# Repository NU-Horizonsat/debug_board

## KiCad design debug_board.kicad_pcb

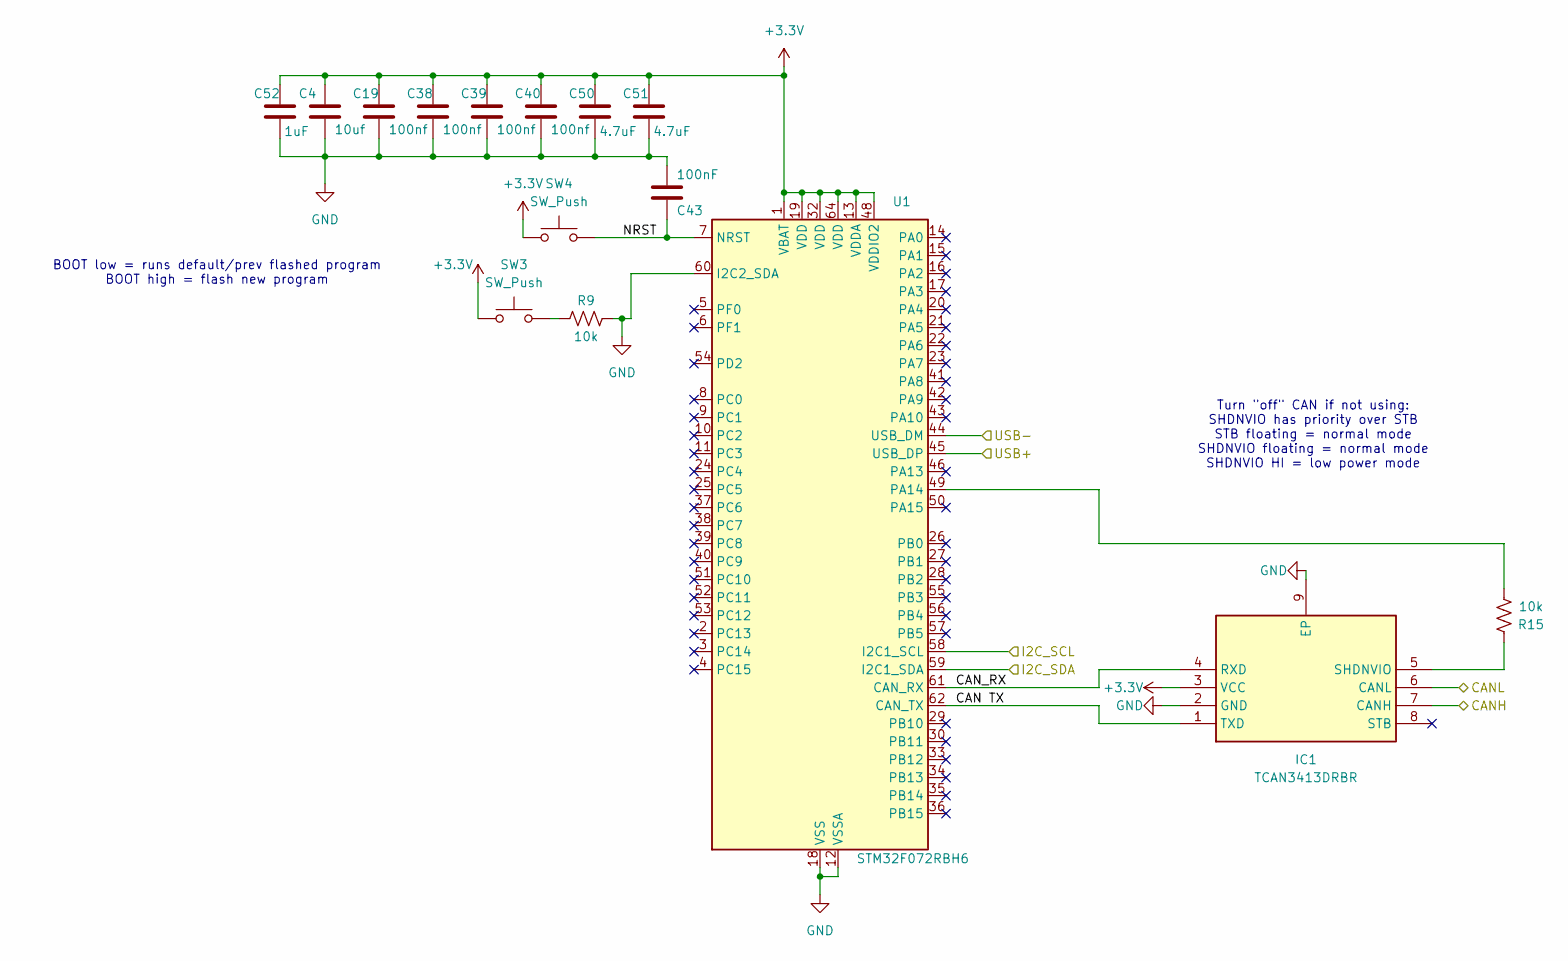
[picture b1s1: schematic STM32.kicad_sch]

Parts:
C4: 10uf; C_0603_1608Metric
C19, C38, C39, C40: 100nf; C_0603_1608Metric
C43: 100nF; C_0603_1608Metric
C50, C51: 4.7uF; C_0603_1608Metric
C52: 1uF; C_0603_1608Metric
IC1: TCAN3413DRBR; SON65P300X300X100-9N-D; Mouser Part Number 595-TCAN3413DRBR
R9, R15: 10k; R_0603_1608Metric
SW3, SW4: SW_Push; SW_Push_1P1T_XKB_TS-1187A
U1: STM32F072RBH6; LQFP-64_10x10mm_P0.5mm

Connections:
+3.3V: C4.1, C19.1, C38.1, C39.1, C40.1, C50.1, C51.1, C52.1, IC1.3 (VCC), SW3.1, SW4.1, U1.1 (VBAT), U1.13 (VDDA), U1.19 (VDD), U1.32 (VDD), U1.48 (VDDIO2), U1.64 (VDD); also elsewhere on the board
/Connector/CANH: IC1.7 (CANH); also elsewhere on the board
/Connector/CANL: IC1.6 (CANL); also elsewhere on the board
/Connector/I2C_SCL: U1.58 (I2C1_SCL); also elsewhere on the board
/Connector/I2C_SDA: U1.59 (I2C1_SDA); also elsewhere on the board
/STM32/CAN TX: IC1.1 (TXD), U1.62 (CAN_TX)
/STM32/CAN_RX: IC1.4 (RXD), U1.61 (CAN_RX)
/STM32/NRST: C43.2, SW4.2, U1.7 (NRST)
/STM32/USB+: U1.45 (USB_DP); also elsewhere on the board
/STM32/USB-: U1.44 (USB_DM); also elsewhere on the board
GND: C4.2, C19.2, C38.2, C39.2, C40.2, C43.1, C50.2, C51.2, C52.2, IC1.2 (GND), IC1.9 (EP), R9.2, U1.12 (VSSA), U1.18 (VSS), U1.31 (VSS), U1.47 (VSS), U1.60 (I2C2_SDA), U1.63 (VSS); also elsewhere on the board
unnamed: IC1.5 (SHDNVIO), R15.2
unnamed: R9.1, SW3.2
unnamed: R15.1, U1.49 (PA14)

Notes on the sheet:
BOOT low = runs default/prev flashed program BOOT high = flash new program
Turn "off" CAN if not using: SHDNVIO has priority over STB STB floating = normal mode SHDNVIO floating = normal mode SHDNVIO HI = low power mode

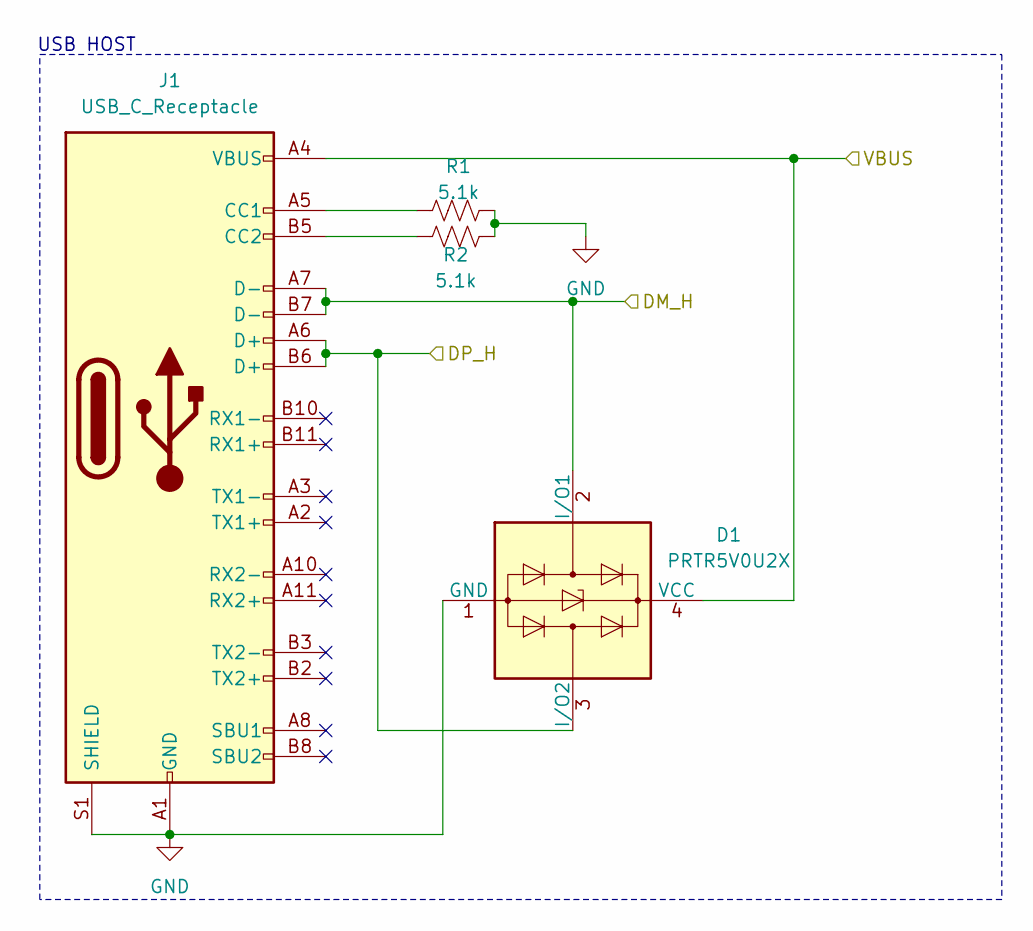
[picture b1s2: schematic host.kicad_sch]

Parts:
D1: PRTR5V0U2X; SOT-143
J1: USB_C_Receptacle; USB_C_Receptacle_HRO_TYPE-C-31-M-12
R1, R2: 5.1k; R_0603_1608Metric

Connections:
/USB Host/DM_H: D1.2 (I/O1), J1.A7 (D-), J1.B7 (D-); also elsewhere on the board
/USB Host/DP_H: D1.3 (I/O2), J1.A6 (D+), J1.B6 (D+); also elsewhere on the board
/USB Host/VBUS: D1.4 (VCC), J1.A4 (VBUS), J1.A9 (VBUS), J1.B4 (VBUS), J1.B9 (VBUS); also elsewhere on the board
GND: D1.1 (GND), J1.A1 (GND), J1.A12 (GND), J1.B1 (GND), J1.B12 (GND), J1.S1 (SHIELD), R1.2, R2.2; also elsewhere on the board
unnamed: J1.A5 (CC1), R1.1
unnamed: J1.B5 (CC2), R2.1

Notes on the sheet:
USB HOST

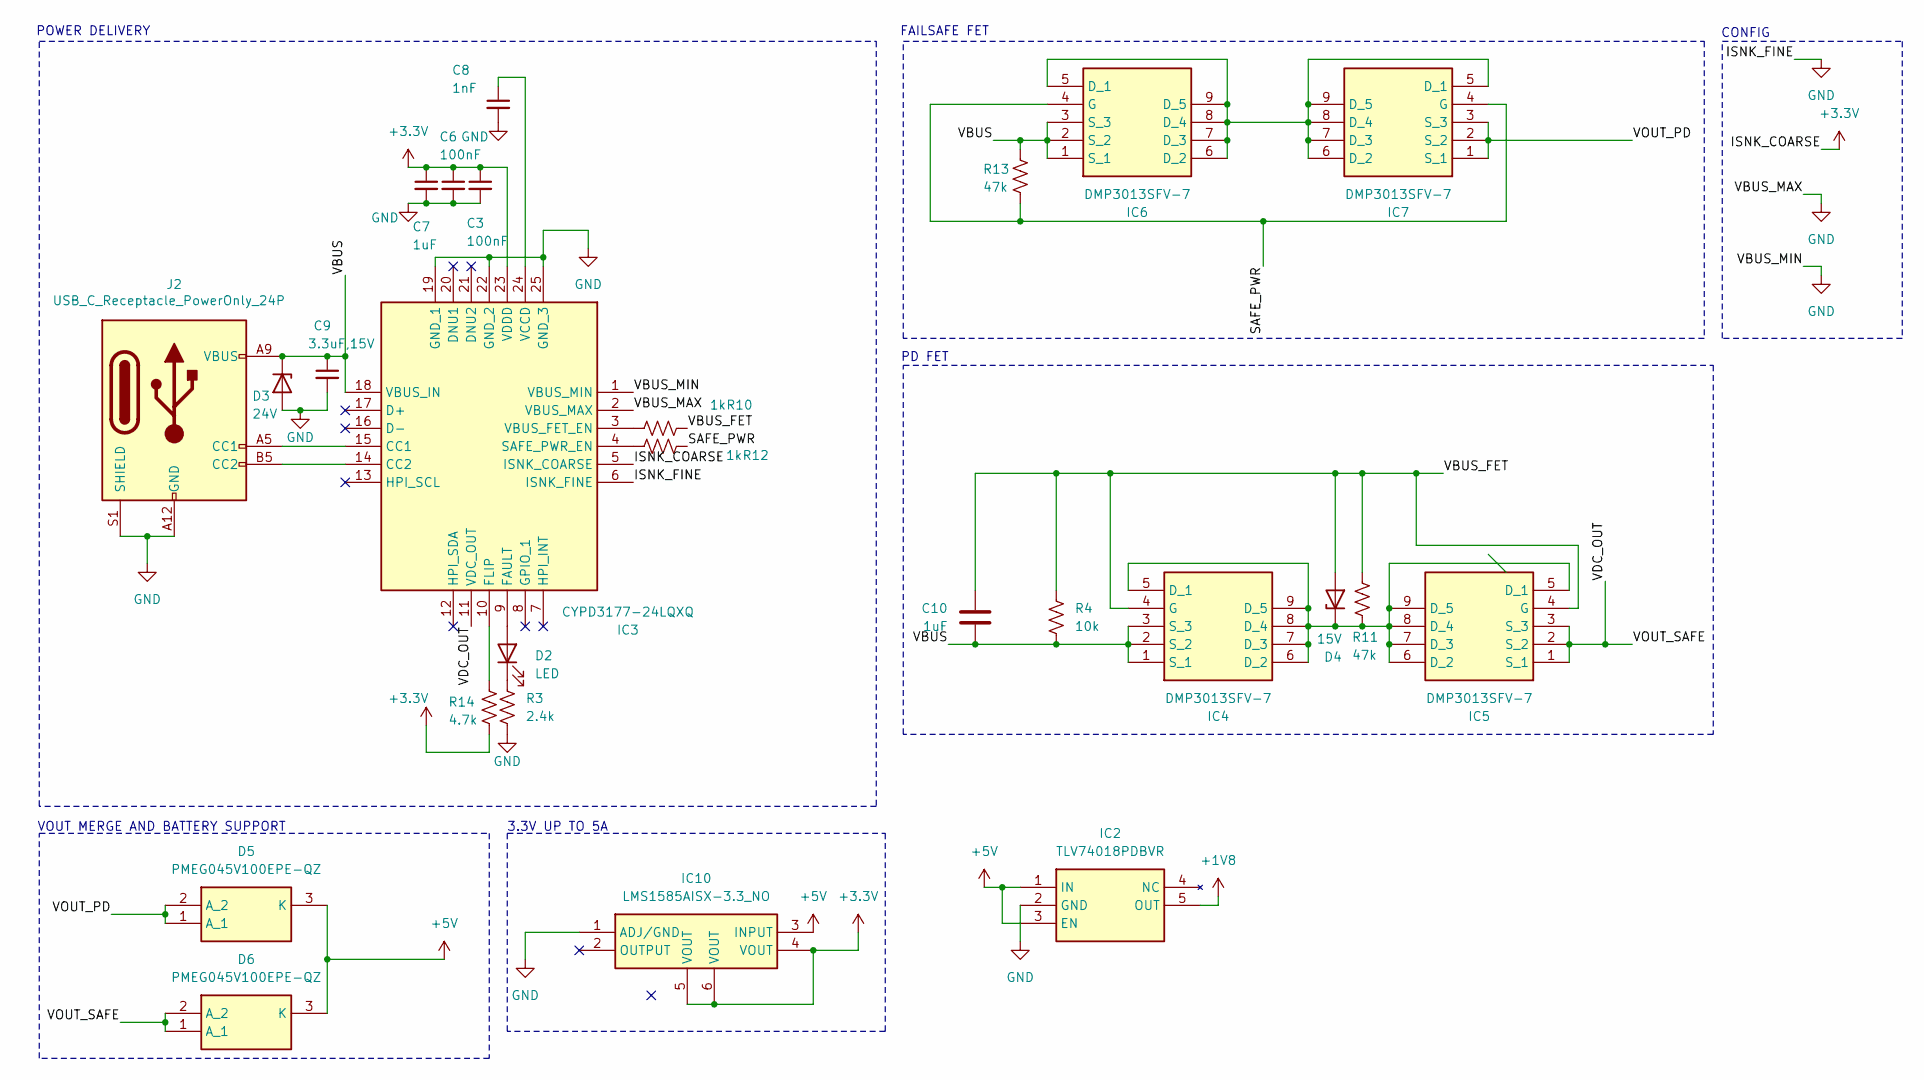
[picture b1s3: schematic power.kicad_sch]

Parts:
C3, C6: 100nF; C_0603_1608Metric
C7, C10: 1uF; C_0603_1608Metric
C8: 1nF; C_0603_1608Metric
C9: 3.3uF,15V; C_0603_1608Metric
D2: LED; LED_0603_1608Metric
D3: 24V; D_SOD-323_HandSoldering
D4: 15V; SODFL2513X100N
D5, D6: PMEG045V100EPE-QZ; PMEG045V100EPEQZ; Mouser Part Number 771-PMEG045V100EPEQZ
IC2: TLV74018PDBVR; SOT95P280X145-5N; Mouser Part Number 595-TLV74018PDBVR
IC3: CYPD3177-24LQXQ; QFN50P400X400X60-25N-D; Mouser Part Number 727-CYPD3177-24LQXQ
IC4, IC5, IC6, IC7: DMP3013SFV-7; DMP3036SFV7; Mouser Part Number 621-DMP3013SFV-7
IC10: LMS1585AISX-3.3_NO; KTT0003B; Mouser Part Number 595-LMS1585AISX33/NO
J2: USB_C_Receptacle_PowerOnly_24P; USB_C_Receptacle_GCT_USB4135-GF-A_6P_TopMnt_Horizontal
R3: 2.4k; R_0603_1608Metric
R4: 10k; R_0603_1608Metric
R10, R12: 1k; R_0603_1608Metric
R11, R13: 47k; R_0603_1608Metric
R14: 4.7k; R_0603_1608Metric

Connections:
+1V8: IC2.5 (OUT); also elsewhere on the board
+3.3V: C3.1, C6.1, C7.1, IC3.5 (ISNK_COARSE), IC3.23 (VDDD), IC10.4 (VOUT), IC10.5 (VOUT), IC10.6 (VOUT), R14.2; also elsewhere on the board
+5V: D5.3 (K), D6.3 (K), IC2.1 (IN), IC2.3 (EN), IC10.3 (INPUT); also elsewhere on the board
/Power/SAFE_PWR: IC6.4 (G), IC7.4 (G), R12.2, R13.2
/Power/VBUS: C9.1, C10.2, D3.1 (K), IC3.18 (VBUS_IN), IC4.1 (S_1), IC4.2 (S_2), IC4.3 (S_3), IC6.1 (S_1), IC6.2 (S_2), IC6.3 (S_3), J2.A4 (VBUS), J2.A9 (VBUS), J2.B4 (VBUS), J2.B9 (VBUS), R4.2, R13.1
/Power/VBUS_FET: C10.1, D4.2 (A), IC4.4 (G), IC5.4 (G), R4.1, R10.2, R11.1
/Power/VDC_OUT: D6.1 (A_1), D6.2 (A_2), IC3.11 (VDC_OUT), IC5.1 (S_1), IC5.2 (S_2), IC5.3 (S_3)
/Power/VOUT_PD: D5.1 (A_1), D5.2 (A_2), IC7.1 (S_1), IC7.2 (S_2), IC7.3 (S_3)
GND: C3.2, C6.2, C7.2, C8.2, C9.2, D3.2 (A), IC2.2 (GND), IC3.1 (VBUS_MIN), IC3.2 (VBUS_MAX), IC3.6 (ISNK_FINE), IC3.19 (GND_1), IC3.22 (GND_2), IC3.25 (GND_3), IC10.1 (ADJ/GND), J2.A1 (GND), J2.A12 (GND), J2.B1 (GND), J2.B12 (GND), J2.S1 (SHIELD), R3.2; also elsewhere on the board
unnamed: D2.2 (A), IC3.9 (FAULT)
unnamed: D2.1 (K), R3.1
unnamed: D4.1 (K), IC4.5 (D_1), IC4.6 (D_2), IC4.7 (D_3), IC4.8 (D_4), IC4.9 (D_5), IC5.5 (D_1), IC5.6 (D_2), IC5.7 (D_3), IC5.8 (D_4), IC5.9 (D_5), R11.2
unnamed: IC3.15 (CC1), J2.A5 (CC1)
unnamed: IC3.14 (CC2), J2.B5 (CC2)
unnamed: IC3.10 (FLIP), R14.1
unnamed: IC3.4 (SAFE_PWR_EN), R12.1
unnamed: IC3.3 (VBUS_FET_EN), R10.1
unnamed: C8.1, IC3.24 (VCCD)
unnamed: IC6.5 (D_1), IC6.6 (D_2), IC6.7 (D_3), IC6.8 (D_4), IC6.9 (D_5), IC7.5 (D_1), IC7.6 (D_2), IC7.7 (D_3), IC7.8 (D_4), IC7.9 (D_5)

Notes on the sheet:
PD FET
POWER DELIVERY
VOUT MERGE AND BATTERY SUPPORT
CONFIG
3.3V UP TO 5A
FAILSAFE FET

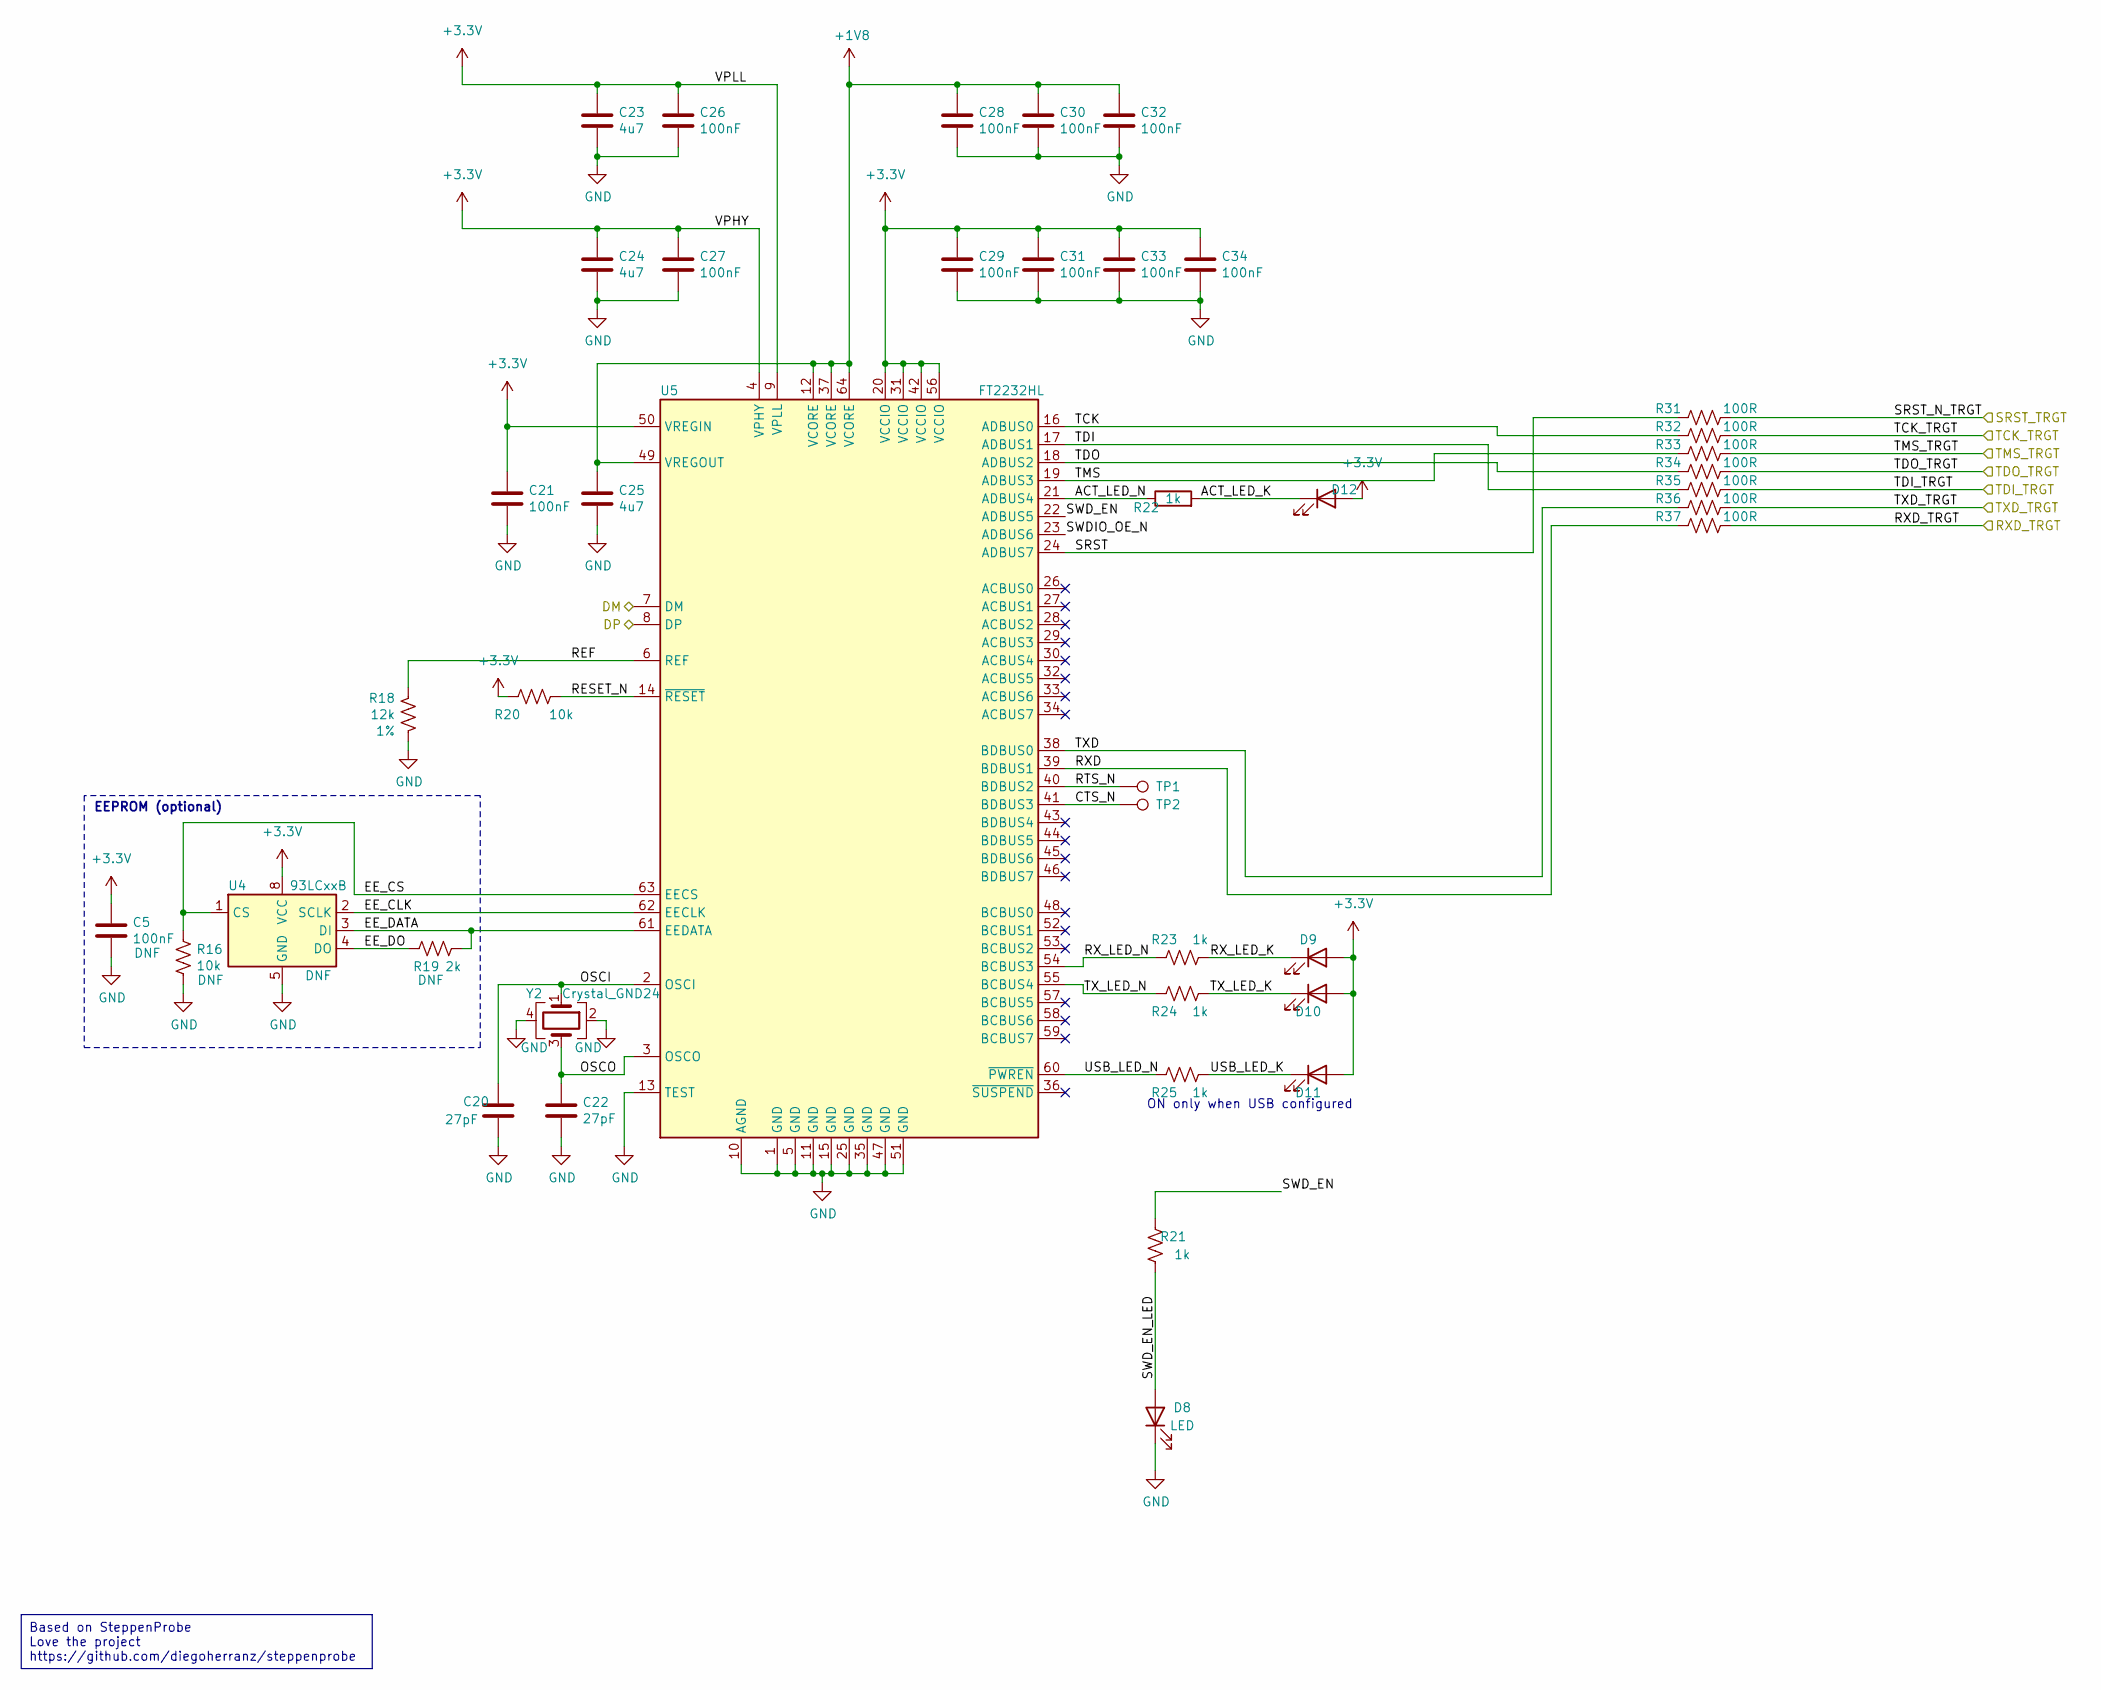
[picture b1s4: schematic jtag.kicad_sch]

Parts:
C5: 100nF; C_0603_1608Metric
C20, C22: 27pF; C_0603_1608Metric; Tolerance 5%; MPN C0603C270J5GAC; LCSC_PN C1656
C21, C26, C27, C28, C29, C30, C31, C32, C33, C34: 100nF; C_0603_1608Metric; Tolerance 10%; MPN CC0603KRX7R9BB104; LCSC_PN C14663
C23, C24, C25: 4u7; C_0603_1608Metric; Tolerance 10%; MPN CL10A475KO8NNNC; LCSC_PN C19666
D8, D9, D10, D11, D12: LED; LED_0603_1608Metric; MPN 19-217/GHC-YR1S2/3T; LCSC_PN C72043
R16: 10k; R_0603_1608Metric
R18: 12k; R_0603_1608Metric; Tolerance 1%; LCSC_PN C22790
R19: 2k; R_0603_1608Metric
R20: 10k; R_0603_1608Metric; Tolerance 5%; LCSC_PN C25804
R21, R22, R23, R24, R25: 1k; R_0603_1608Metric; Tolerance 5%; LCSC_PN C21190
R31, R32, R33, R34, R35, R36, R37: 100R; R_0603_1608Metric; Tolerance 5%; LCSC_PN C22775
TP1, TP2: TestPoint; TestPoint_Pad_D1.0mm
U4: 93LCxxB; SOIC-8_3.9x4.9mm_P1.27mm
U5: FT2232HL; LQFP-64_10x10mm_P0.5mm; MPN FT2232HL; LCSC_PN C27882
Y2: Crystal_GND24; Crystal_SMD_3225-4Pin_3.2x2.5mm; Tolerance 10PPM; MPN ABM8-12.000MHZ-20-B1U-T; LCSC_PN C9002

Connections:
+1V8: C25.1, C28.1, C30.1, C32.1, U5.12 (VCORE), U5.37 (VCORE), U5.49 (VREGOUT), U5.64 (VCORE); also elsewhere on the board
+3.3V: C5.1, C21.1, C23.1, C24.1, C26.1, C27.1, C29.1, C31.1, C33.1, C34.1, D9.2 (A), D10.2 (A), D11.2 (A), D12.2 (A), R20.2, U4.8 (VCC), U5.4 (VPHY), U5.9 (VPLL), U5.20 (VCCIO), U5.31 (VCCIO), U5.42 (VCCIO), U5.50 (VREGIN), U5.56 (VCCIO); also elsewhere on the board
/FTDI/ACT_LED_K: D12.1 (K), R22.2
/FTDI/ACT_LED_N: R22.1, U5.21 (ADBUS4)
/FTDI/CTS_N: TP2.1, U5.41 (BDBUS3)
/FTDI/DM: U5.7 (DM); also elsewhere on the board
/FTDI/DP: U5.8 (DP); also elsewhere on the board
/FTDI/EE_CLK: U4.2 (SCLK), U5.62 (EECLK)
/FTDI/EE_CS: R16.1, U4.1 (CS), U5.63 (EECS)
/FTDI/EE_DATA: R19.2, U4.3 (DI), U5.61 (EEDATA)
/FTDI/EE_DO: R19.1, U4.4 (DO)
/FTDI/OSCI: C20.1, U5.2 (OSCI), Y2.1
/FTDI/OSCO: C22.1, U5.3 (OSCO), Y2.3
/FTDI/REF: R18.1, U5.6 (REF)
/FTDI/RESET_N: R20.1, U5.14 (~RESET)
/FTDI/RTS_N: TP1.1, U5.40 (BDBUS2)
/FTDI/RXD: R37.1, U5.39 (BDBUS1)
/FTDI/RXD_TRGT: R37.2; also elsewhere on the board
/FTDI/RX_LED_K: D9.1 (K), R23.1
/FTDI/RX_LED_N: R23.2, U5.54 (BCBUS3)
/FTDI/SRST: R31.2, U5.24 (ADBUS7)
/FTDI/SRST_N_TRGT: R31.1; also elsewhere on the board
/FTDI/SWDIO_OE_N: U5.23 (ADBUS6)
/FTDI/SWD_EN: R21.2, U5.22 (ADBUS5)
/FTDI/SWD_EN_LED: D8.2 (A), R21.1
/FTDI/TCK: R32.2, U5.16 (ADBUS0)
/FTDI/TCK_TRGT: R32.1; also elsewhere on the board
/FTDI/TDI: R35.2, U5.17 (ADBUS1)
/FTDI/TDI_TRGT: R35.1; also elsewhere on the board
/FTDI/TDO: R34.2, U5.18 (ADBUS2)
/FTDI/TDO_TRGT: R34.1; also elsewhere on the board
/FTDI/TMS: R33.2, U5.19 (ADBUS3)
/FTDI/TMS_TRGT: R33.1; also elsewhere on the board
/FTDI/TXD: R36.2, U5.38 (BDBUS0)
/FTDI/TXD_TRGT: R36.1; also elsewhere on the board
/FTDI/TX_LED_K: D10.1 (K), R24.1
/FTDI/TX_LED_N: R24.2, U5.55 (BCBUS4)
/FTDI/USB_LED_K: D11.1 (K), R25.1
/FTDI/USB_LED_N: R25.2, U5.60 (~PWREN)
GND: C5.2, C20.2, C21.2, C22.2, C23.2, C24.2, C25.2, C26.2, C27.2, C28.2, C29.2, C30.2, C31.2, C32.2, C33.2, C34.2, D8.1 (K), R16.2, R18.2, U4.5 (GND), U5.1 (GND), U5.5 (GND), U5.10 (AGND), U5.11 (GND), U5.13 (TEST), U5.15 (GND), U5.25 (GND), U5.35 (GND), U5.47 (GND), U5.51 (GND), Y2.2, Y2.4; also elsewhere on the board

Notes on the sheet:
Based on SteppenProbe Love the project https://github.com/diegoherranz/steppenprobe
EEPROM (optional)
ON only when USB configured

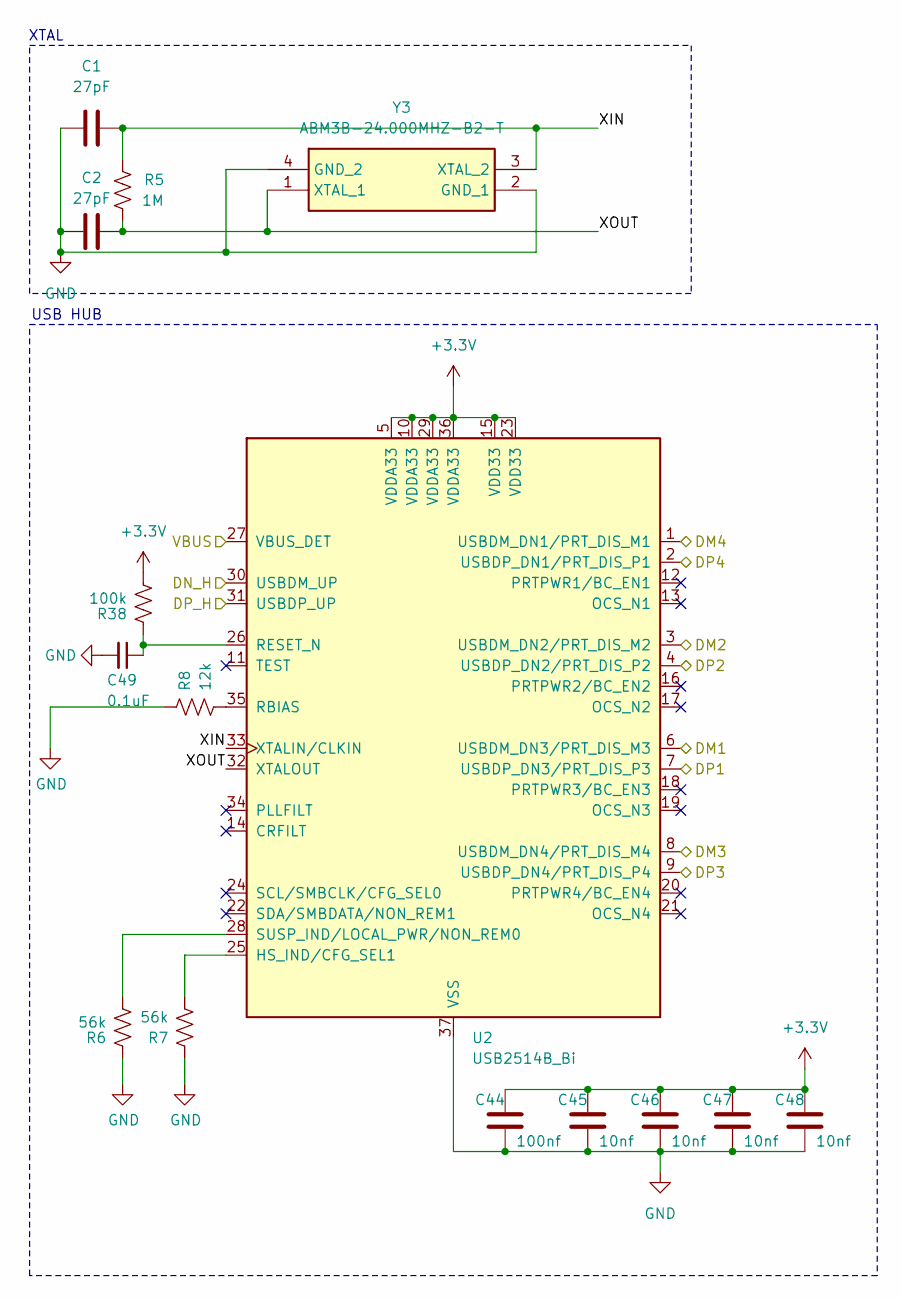
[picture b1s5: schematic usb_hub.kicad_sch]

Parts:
C1, C2: 27pF; C_0603_1608Metric
C44: 100nf; C_0603_1608Metric
C45, C46, C47, C48: 10nf; C_0603_1608Metric
C49: 0.1uF; C_0402_1005Metric
R5: 1M; R_0603_1608Metric
R6, R7: 56k; R_0603_1608Metric
R8: 12k; R_0603_1608Metric
R38: 100k; R_0603_1608Metric
U2: USB2514B_Bi; QFN-36-1EP_6x6mm_P0.5mm_EP3.7x3.7mm
Y3: ABM3B-24.000MHZ-B2-T; ABM3B; Mouser Part Number 815-ABM3B-24-B2

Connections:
+3.3V: C44.1, C45.1, C46.1, C47.1, C48.1, R38.2, U2.5 (VDDA33), U2.10 (VDDA33), U2.15 (VDD33), U2.23 (VDD33), U2.29 (VDDA33), U2.36 (VDDA33); also elsewhere on the board
/Connector/USB2+?: U2.9 (USBDP_DN4/PRT_DIS_P4); also elsewhere on the board
/Connector/USB2-?: U2.8 (USBDM_DN4/PRT_DIS_M4); also elsewhere on the board
/Connector/USB+: U2.4 (USBDP_DN2/PRT_DIS_P2); also elsewhere on the board
/Connector/USB-: U2.3 (USBDM_DN2/PRT_DIS_M2); also elsewhere on the board
/FTDI/DM: U2.6 (USBDM_DN3/PRT_DIS_M3); also elsewhere on the board
/FTDI/DP: U2.7 (USBDP_DN3/PRT_DIS_P3); also elsewhere on the board
/STM32/USB+: U2.2 (USBDP_DN1/PRT_DIS_P1); also elsewhere on the board
/STM32/USB-: U2.1 (USBDM_DN1/PRT_DIS_M1); also elsewhere on the board
/USB Host/DM_H: U2.30 (USBDM_UP); also elsewhere on the board
/USB Host/DP_H: U2.31 (USBDP_UP); also elsewhere on the board
/USB Host/VBUS: U2.27 (VBUS_DET); also elsewhere on the board
/USB Hub/XIN: C1.2, R5.1, U2.33 (XTALIN/CLKIN), Y3.3 (XTAL_2)
/USB Hub/XOUT: C2.2, R5.2, U2.32 (XTALOUT), Y3.1 (XTAL_1)
GND: C1.1, C2.1, C44.2, C45.2, C46.2, C47.2, C48.2, C49.2, R6.1, R7.1, R8.1, U2.37 (VSS), Y3.2 (GND_1), Y3.4 (GND_2); also elsewhere on the board
unnamed: R7.2, U2.25 (HS_IND/CFG_SEL1)
unnamed: R8.2, U2.35 (RBIAS)
unnamed: C49.1, R38.1, U2.26 (RESET_N)
unnamed: R6.2, U2.28 (SUSP_IND/LOCAL_PWR/NON_REM0)

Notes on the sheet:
XTAL
USB HUB

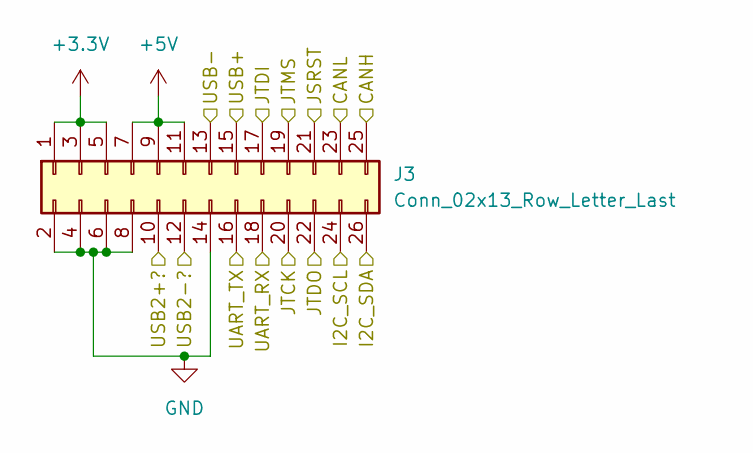
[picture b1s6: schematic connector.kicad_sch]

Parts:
J3: Conn_02x13_Row_Letter_Last; Samtec_HSEC8-113-X-X-DV_2x13_P0.8mm_Edge

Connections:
+3.3V: J3.1, J3.3, J3.5; also elsewhere on the board
+5V: J3.7, J3.9, J3.11; also elsewhere on the board
/Connector/CANH: J3.25; also elsewhere on the board
/Connector/CANL: J3.23; also elsewhere on the board
/Connector/I2C_SCL: J3.24; also elsewhere on the board
/Connector/I2C_SDA: J3.26; also elsewhere on the board
/Connector/USB2+?: J3.10; also elsewhere on the board
/Connector/USB2-?: J3.12; also elsewhere on the board
/Connector/USB+: J3.15; also elsewhere on the board
/Connector/USB-: J3.13; also elsewhere on the board
/FTDI/RXD_TRGT: J3.18; also elsewhere on the board
/FTDI/SRST_N_TRGT: J3.21; also elsewhere on the board
/FTDI/TCK_TRGT: J3.20; also elsewhere on the board
/FTDI/TDI_TRGT: J3.17; also elsewhere on the board
/FTDI/TDO_TRGT: J3.22; also elsewhere on the board
/FTDI/TMS_TRGT: J3.19; also elsewhere on the board
/FTDI/TXD_TRGT: J3.16; also elsewhere on the board
GND: J3.2, J3.4, J3.6, J3.8, J3.14; also elsewhere on the board

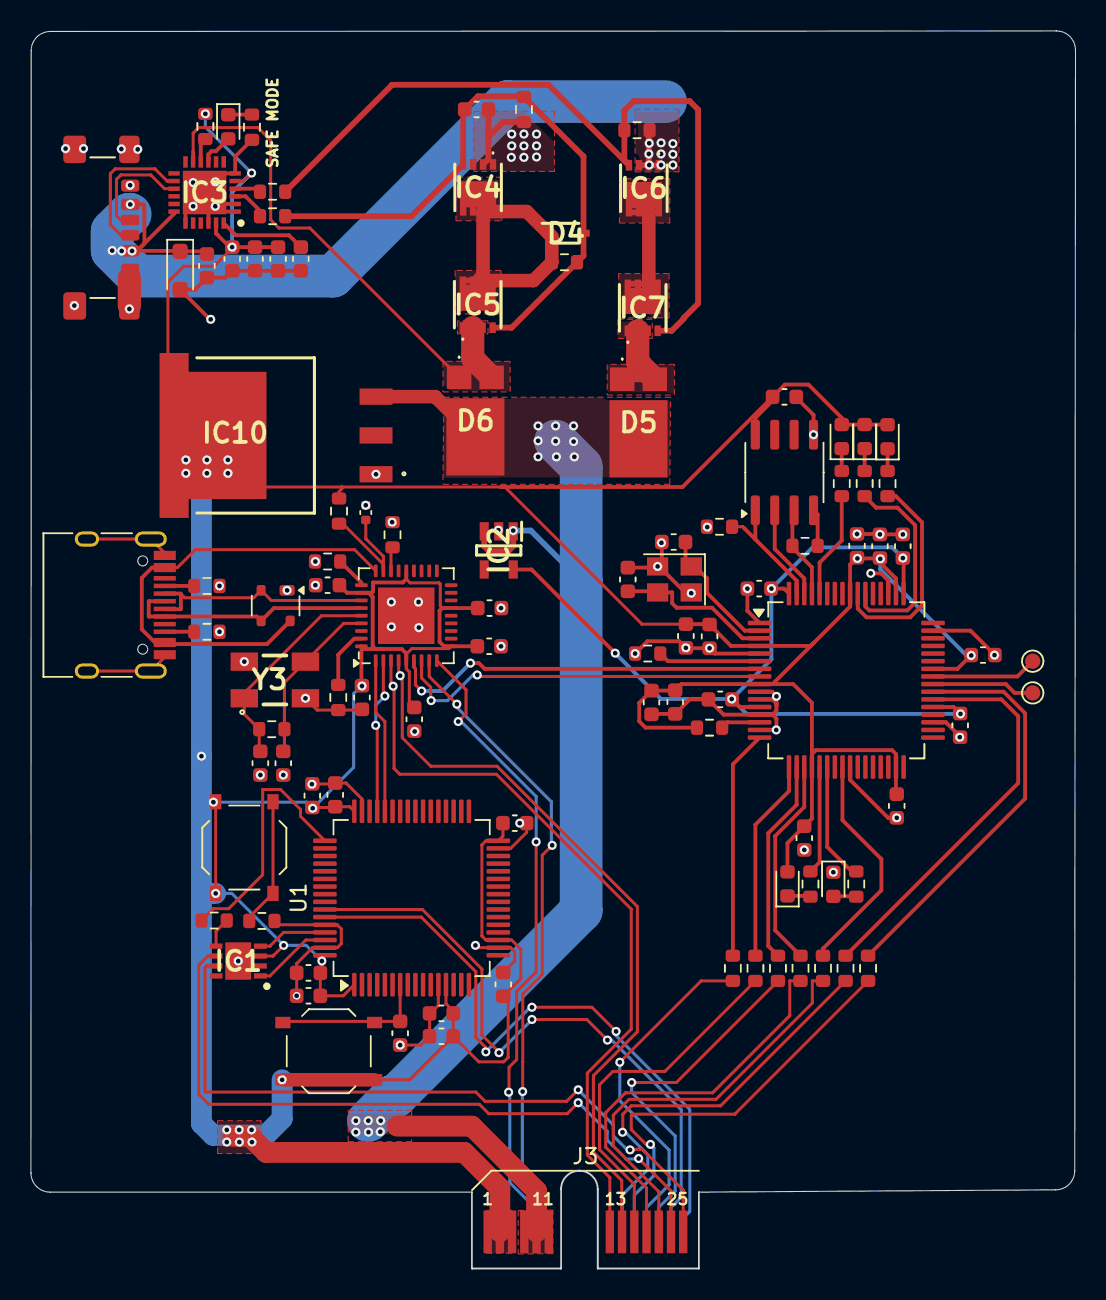
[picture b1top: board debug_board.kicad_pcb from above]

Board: 2 copper layers, 68.3 x 81.0 mm, 103 parts (0 on the bottom side), 82 nets.

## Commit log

2024-06-22 Initial commit
    Need to add power capacitors, UART, and USB to edge connector. Also have to finish JTAG based on this pinout and code: https://jacobncalvert.com/blog-archive/2020/03/05/better-jtag-on-the-cheap-with-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
2024-06-23 changed upstream usb to not power hub. Will add PD usb source later
2024-06-23 Added PD, need to work on a power mux and regulator
2024-06-24 added power mux
2024-06-25 POWER IS DONE!!! need someone to check it
2024-06-27 Used steppenprobe as base for our UART and JTAG.
2024-06-28 updated edge connector
2024-07-04 renamed i2c
2024-07-05 STM32 schematic
2024-07-05 3.3V changes and changed labels to hierarchical one's
2024-07-06 linked everything together. still need to add capacitors
2024-07-20 started pcb layout, host and usbhub done
2024-07-20 routed stm32
2024-07-23 pcb routed!!!!!!!
